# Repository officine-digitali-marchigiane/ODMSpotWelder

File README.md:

# ODMSpotWelder
Spot welder project from Officine Digitali Marchigiane (c) 2019
#  Contributing
Please submit pull requests on branch 'devel'

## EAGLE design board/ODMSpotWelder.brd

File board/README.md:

## Spot welder board
### top

### bottom

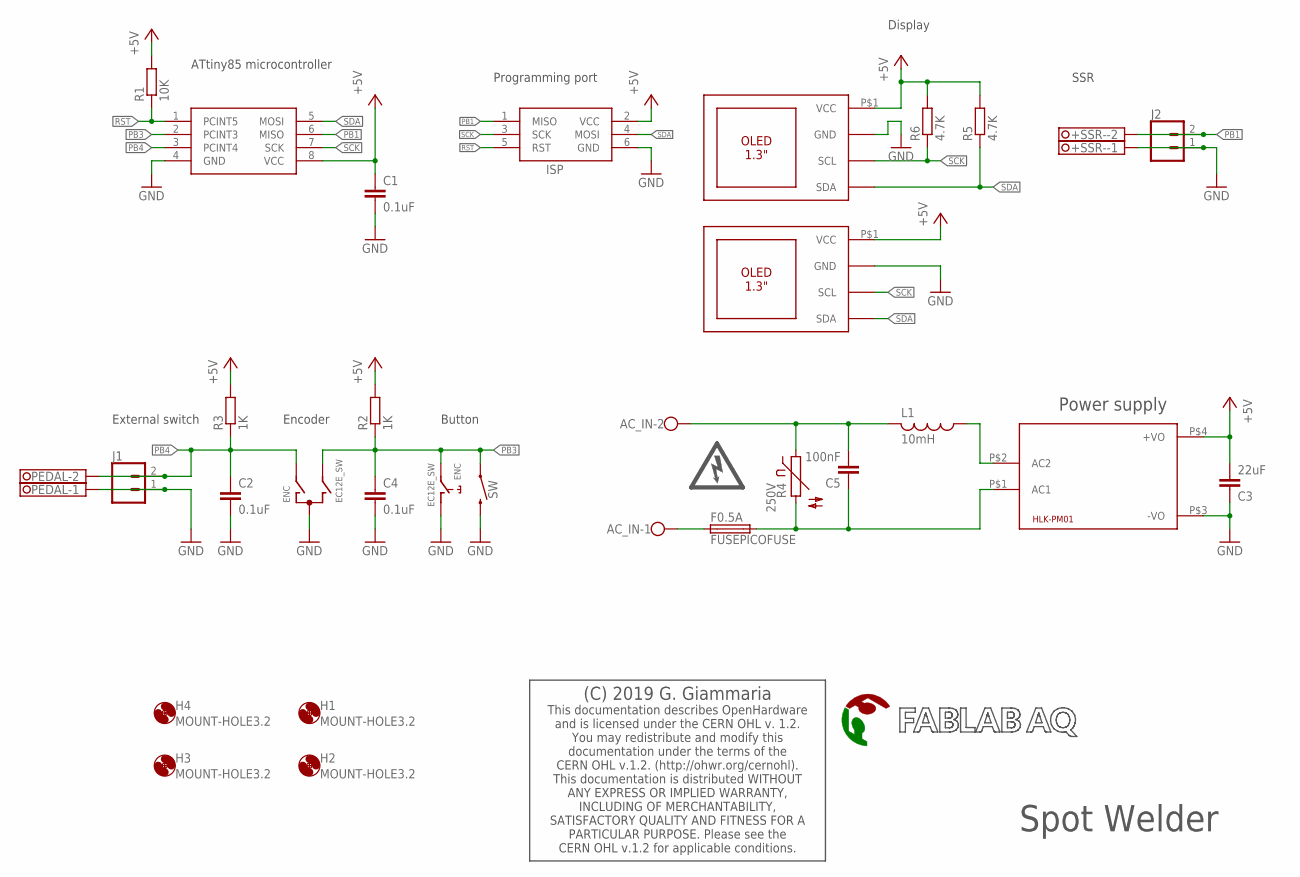
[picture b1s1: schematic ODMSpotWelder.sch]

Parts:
+SSR-: TERMINAL-BLOCK-3.5MM-2-PIN-LONG-PAD; TERMINAL-BLOCK-2-PIN-3.5MM-LONG-PAD
AC_IN: W237-102
C1, C2, C4: 0.1uF; C0603K
C3: 22uF; C0805K
C5: 100nF; C102-064X133
ENC: EC12E_SW; ALPS_EC12E_SW
F0.5A: FUSEPICOFUSE; PICOFUSE
H1, H2, H3, H4: MOUNT-HOLE3.2; 3,2
HLK-PM01: HLK-PM01; HLK-PMXX
IC2: ATTINY85-20SU; SOT127P798X216-8N
ISP: AVRISP-6; AVRISP
J1, J2: CONN_021X02_NO_SILK; 1X02_NO_SILK
L1: 10mH; 6000-XXXX-RC
PEDAL: TERMINAL-BLOCK-3.5MM-2-PIN-LONG-PAD; TERMINAL-BLOCK-2-PIN-3.5MM-LONG-PAD
R1: 10K; R0603
R2, R3: 1K; R0603
R4: 250V; S07K250
R5, R6: 4.7K; R0603
SW: MOMENTARY-SWITCH-SPST-PTH-6.0MM; TACTILE_SWITCH_PTH_6.0MM
U$1: (C) 2019 G. Giammaria; DOC_CERN_OHL_1.2
U$2: HV_SYMBOL; HV_SYMBOL_10X10
U$4: FABLABAQ_LOGOINLINE_4.5X20; SILK_INLINE_4.5X20
U$5: ODM_LOGO; ODM_6X12
U$6, U$7: OLED_1.3_I2C

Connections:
+5V: C1.1, C3.2, HLK-PM01.P$4 (+VO), IC2.8 (VCC), ISP.2 (VCC), R1.2, R2.2, R3.2, R5.2, R6.2, U$6.P$1 (VCC), U$7.P$1 (VCC)
GND: +SSR-.1, C1.2, C2.2, C3.1, C4.2, ENC.C, ENC.D (1), HLK-PM01.P$3 (-VO), IC2.4 (GND), ISP.6 (GND), J1.1, J2.1, PEDAL.1, SW.3 (2), U$6.P$2 (GND), U$7.P$2 (GND)
unnamed: HLK-PM01.P$2 (AC2), L1.1
unnamed: AC_IN.2, C5.2, L1.2, R4.1
unnamed: AC_IN.1, F0.5A.1
unnamed: C5.1, F0.5A.2, HLK-PM01.P$1 (AC1), R4.2
PB1: +SSR-.2, IC2.6 (MISO), ISP.1 (MISO), J2.2
PB3: C4.1, ENC.B, ENC.E (2), IC2.2 (PCINT3), R2.1, SW.1
PB4: C2.1, ENC.A, IC2.3 (PCINT4), J1.2, PEDAL.2, R3.1
RST: IC2.1 (PCINT5), ISP.5 (RST), R1.1
SCK: IC2.7 (SCK), ISP.3 (SCK), R6.1, U$6.P$3 (SCL), U$7.P$3 (SCL)
SDA: IC2.5 (MOSI), ISP.4 (MOSI), R5.1, U$6.P$4 (SDA), U$7.P$4 (SDA)

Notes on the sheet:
Power supply
Programming port
ATtiny85 microcontroller
Button
External switch
Display
Encoder
Spot Welder
SSR

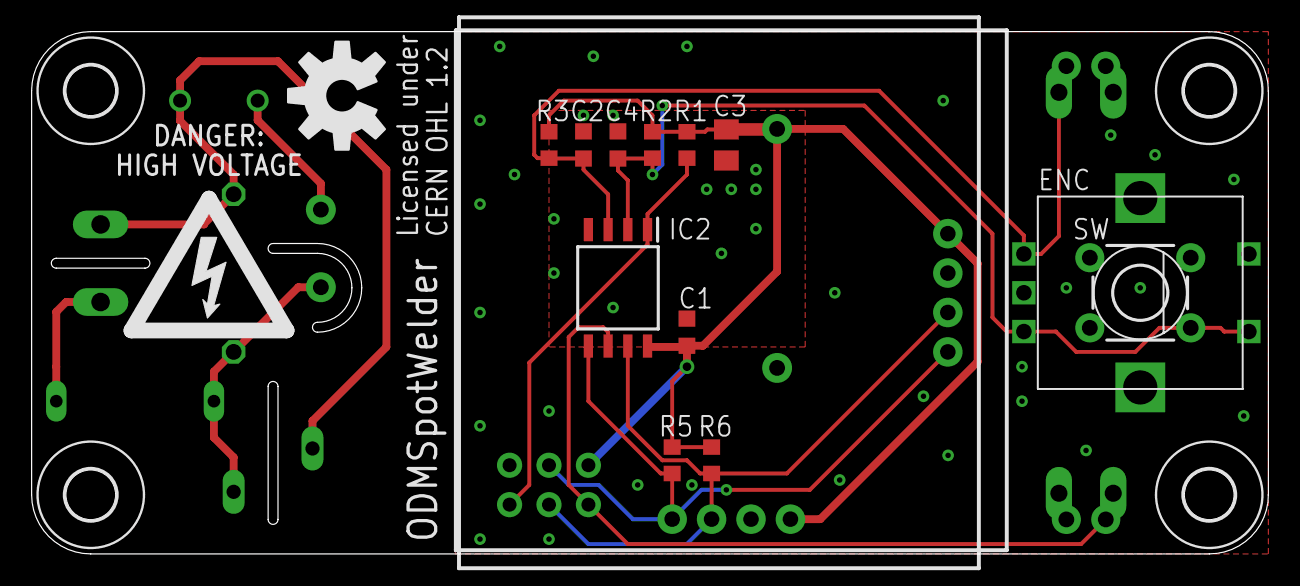
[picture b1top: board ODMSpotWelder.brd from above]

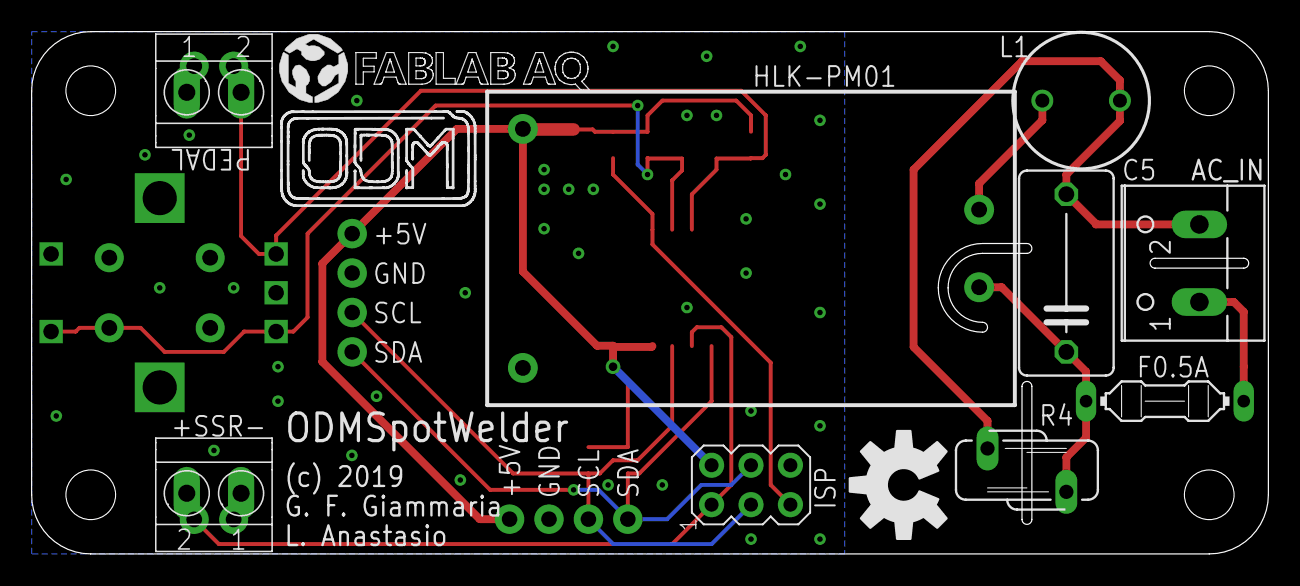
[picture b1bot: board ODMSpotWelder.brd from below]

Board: 2 copper layers, 79.7 x 33.7 mm, 35 parts (12 on the bottom side), 12 nets.

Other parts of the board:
U$3, U$8: OSHW-LOGO-L

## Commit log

2019-02-28 Minor changes
2019-02-28 Added OneButton library
2019-03-11 Allineato con la simulazione
2019-03-11 README modified
2019-03-13 added board design files
2019-03-25 aggiunta gestione del debounce con la libreria OneButton
2019-04-01 Added oversampling

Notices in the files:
board/ODMSpotWelder.brd:
Licensed under
CERN OHL 1.2
parts and their libraries:
SparkFun-Aesthetics: Licensing: Creative Commons ShareAlike 4.0 International - https://creativecommons.org/licenses/by-sa/4.0
CERN_OHL_1.2: and is licensed under the CERN OHL v. 1.2.
documentation under the terms of the
CERN OHL v.1.2. (http://ohwr.org/cernohl).
